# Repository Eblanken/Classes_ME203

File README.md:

# Classes_ME203
CAD and ECAD files for the ME203 manufacturing class.

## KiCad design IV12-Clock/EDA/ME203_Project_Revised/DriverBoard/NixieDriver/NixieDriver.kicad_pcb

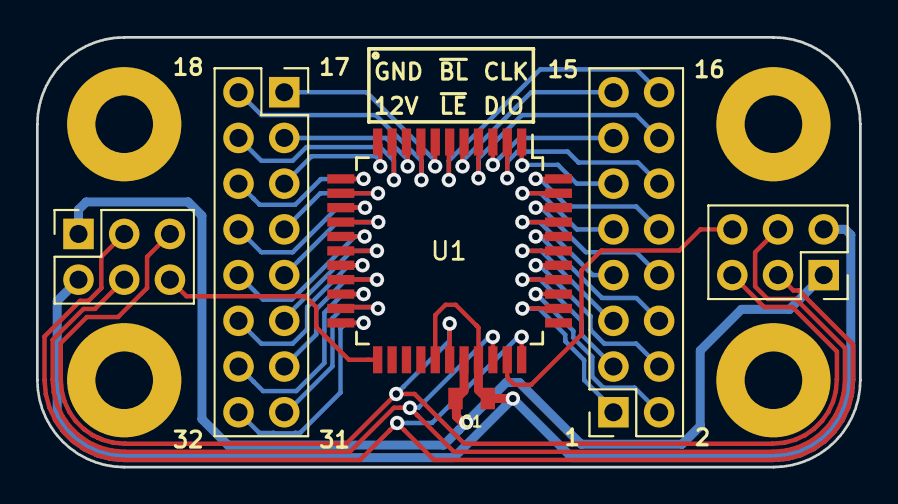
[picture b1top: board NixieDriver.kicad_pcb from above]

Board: 2 copper layers, 45.7 x 23.9 mm, 10 parts (0 on the bottom side), 39 nets.

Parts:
C1: 0.1UF-0805-100V; 0805
H1, H2, H3, H4: STANDOFF_ELECTRICAL; STANDOFF-ELECTRICAL
J1, J4: Conn_02x08_Counter_Clockwise; PinSocket_2x08_P2.54mm_Vertical
J2, J3: Conn_01x06; PinSocket_2x03_P2.54mm_Vertical
U1: HV5530PG-G-44PQF; PQFP-44_10x10mm_P0.8mm

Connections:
+12V: C1.1, J2.2, J3.2, U1.27, U1.30
/CLK: J2.5, J3.5, U1.28
/DI: J3.6, U1.32
/DO: J2.6, U1.23
/~BL: J2.3, J3.3, U1.33
/~LE: J2.4, J3.4, U1.31
GND: C1.2, J2.1, J3.1, U1.29
unnamed: J1.1, U1.7
unnamed: J1.2, U1.8
unnamed: J1.3, U1.9
unnamed: J1.4, U1.10
unnamed: J1.5, U1.11
unnamed: J1.6, U1.12
unnamed: J1.7, U1.13
unnamed: J1.8, U1.14
unnamed: J1.9, U1.15
unnamed: J1.10, U1.16
unnamed: J1.11, U1.17
unnamed: J1.12, U1.18
unnamed: J1.13, U1.19
unnamed: J1.14, U1.20
unnamed: J1.15, U1.21
unnamed: J1.16, U1.22
unnamed: J4.1, U1.35
unnamed: J4.2, U1.36
unnamed: J4.3, U1.37
unnamed: J4.4, U1.38
unnamed: J4.5, U1.39
unnamed: J4.6, U1.40
unnamed: J4.7, U1.41
unnamed: J4.8, U1.42
unnamed: J4.9, U1.43
unnamed: J4.10, U1.44
unnamed: J4.11, U1.1
unnamed: J4.12, U1.2
unnamed: J4.13, U1.3
unnamed: J4.14, U1.4
unnamed: J4.15, U1.5
unnamed: J4.16, U1.6

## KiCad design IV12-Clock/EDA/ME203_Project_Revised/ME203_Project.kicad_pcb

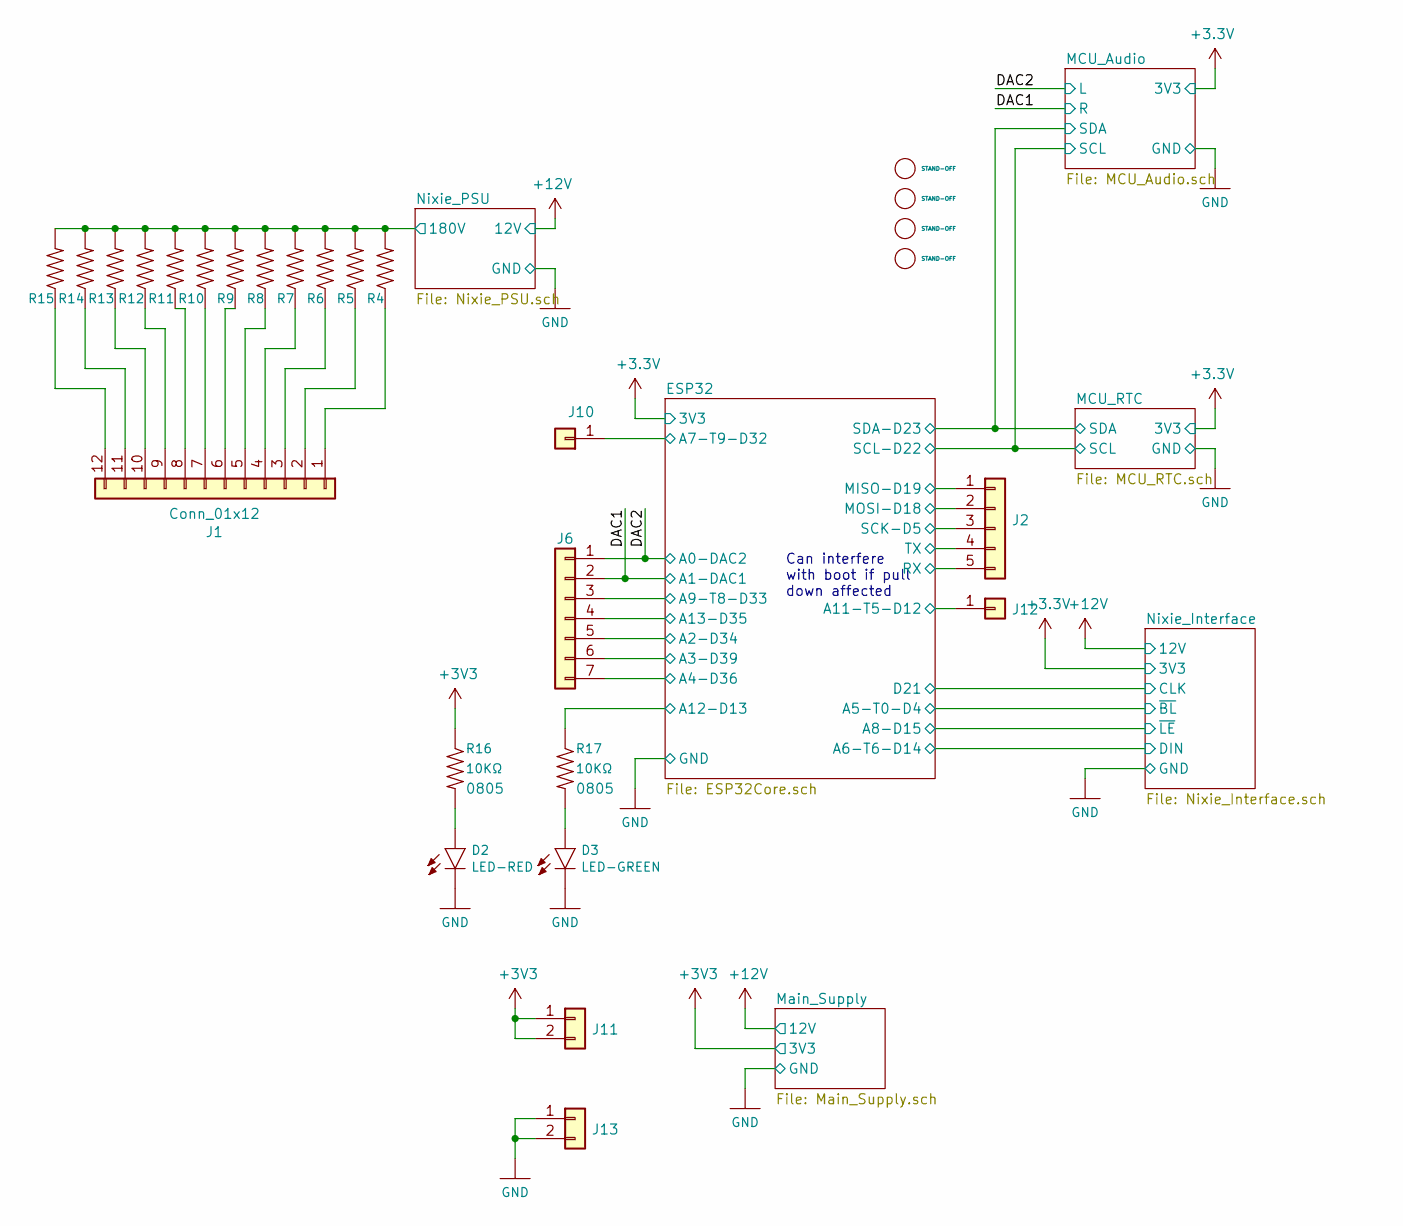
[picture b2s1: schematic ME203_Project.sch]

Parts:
D2: LED-RED; LED-0603
D3: LED-GREEN; LED-0603
H1, H2, H3, H4: STAND-OFF
J1: Conn_01x12; PinSocket_2x06_P2.54mm_Vertical
J2: Conn_01x05; PinHeader_1x05_P2.54mm_Vertical
J6: Conn_01x07; PinHeader_1x07_P2.54mm_Vertical
J10, J12: Conn_01x01; PinHeader_1x01_P2.54mm_Vertical
J11, J13: Conn_01x02; PinHeader_1x02_P2.54mm_Vertical
R4, R5, R6, R7, R8, R9, R10, R11, R12, R13, R14, R15: RESISTOR0805; 0805
R16, R17: 10KΩ; 0805

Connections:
+3V3: J11.1, J11.2, R16.1; also elsewhere on the board
/DAC1: J6.2; also elsewhere on the board
/DAC2: J6.1; also elsewhere on the board
/ESP32/A2-D34: J6.5; also elsewhere on the board
/ESP32/A3-D39: J6.6; also elsewhere on the board
/ESP32/A4-D36: J6.7; also elsewhere on the board
/ESP32/A7-T9-D32: J10.1; also elsewhere on the board
/ESP32/A9-T8-D33: J6.3; also elsewhere on the board
/ESP32/A11-T5-D12: J12.1; also elsewhere on the board
/ESP32/A12-D13: R17.1; also elsewhere on the board
/ESP32/A13-D35: J6.4; also elsewhere on the board
/ESP32/MISO-D19: J2.1; also elsewhere on the board
/ESP32/MOSI-D18: J2.2; also elsewhere on the board
/ESP32/RX: J2.5; also elsewhere on the board
/ESP32/SCK-D5: J2.3; also elsewhere on the board
/ESP32/TX: J2.4; also elsewhere on the board
/Nixie_PSU/180V: R4.2, R5.2, R6.2, R7.2, R8.2, R9.2, R10.2, R11.2, R12.2, R13.2, R14.2, R15.2; also elsewhere on the board
GND: D2.C, D3.C, J13.1, J13.2; also elsewhere on the board
unnamed: D2.A, R16.2
unnamed: D3.A, R17.2
unnamed: J1.1, R4.1
unnamed: J1.2, R5.1
unnamed: J1.3, R6.1
unnamed: J1.4, R7.1
unnamed: J1.5, R8.1
unnamed: J1.6, R9.1
unnamed: J1.7, R10.1
unnamed: J1.8, R11.1
unnamed: J1.9, R12.1
unnamed: J1.10, R13.1
unnamed: J1.11, R14.1
unnamed: J1.12, R15.1

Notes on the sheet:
Can interfere with boot if pull down affected

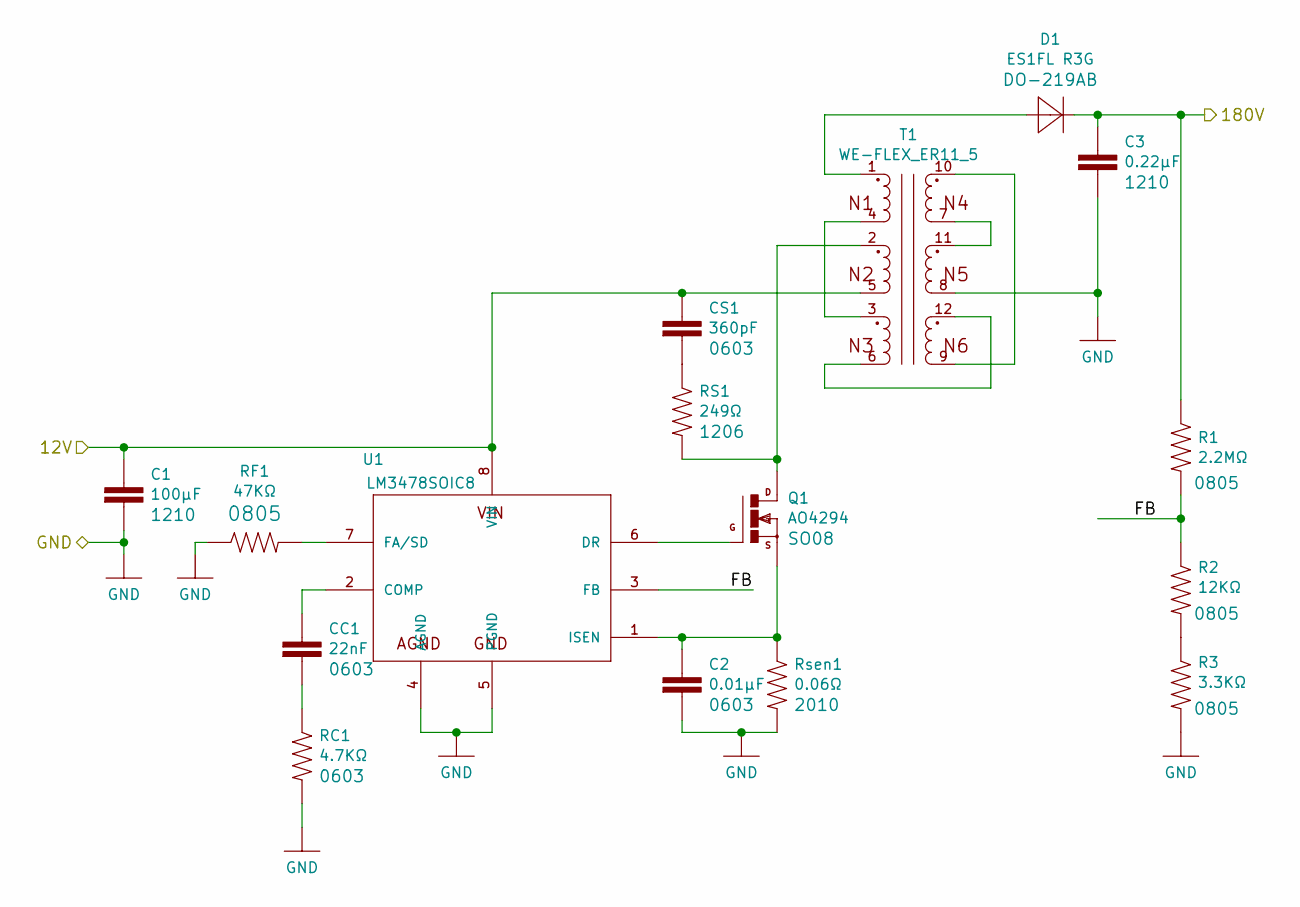
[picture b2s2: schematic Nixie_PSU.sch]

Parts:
C1: 100µF; C_1210_3225Metric; Digikey 311-2052-1-ND
C2: 0.01µF; C_0603_1608Metric; Digikey 311-3369-1-ND
C3: 0.22µF; C_1210_3225Metric; Digikey 445-2296-1-ND
CC1: 22nF; C_0603_1608Metric; Digikey 732-7935-1-ND
CS1: 360pF; C_0603_1608Metric; Digikey 490-1364-1-ND
D1: ES1FL R3G; nixiemisc-DO-219AB; Digikey ES1FL R3GCT-ND
Q1: AO4294; nixiemisc-SO-08; Digikey 785-1732-1-ND
R1: 2.2MΩ; 0603
R2: 12KΩ; 0805
R3: 3.3KΩ; 0805
RC1: 4.7KΩ; R_0603_1608Metric; Digikey RMCF0805FT4K70CT-ND
RF1: 47KΩ; R_0805_2012Metric; Digikey RMCF0805FT47K0CT-ND
RS1: 249Ω; R_1206_3216Metric; Digikey RNCP1206FTD249RCT-ND
Rsen1: 0.06Ω; R_2010_5025Metric; Digikey CSRN2010FK60L0CT-ND
T1: WE-FLEX_ER11_5; nixiemisc-WE-FLEX_ER11_5; Digikey 1297-1196-1-ND
U1: LM3478SOIC8; nixiemisc-SOIC8; Digikey 296-38111-1-ND

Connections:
+12V: C1.1, CS1.1, T1.5 (10), U1.8 (VIN); also elsewhere on the board
/Nixie_PSU/180V: C3.1, D1.C, R1.1; also elsewhere on the board
/Nixie_PSU/FB: R1.2, R2.1, U1.3 (FB)
GND: C1.2, C2.2, C3.2, R3.2, RC1.2, RF1.1, Rsen1.2, T1.8 (5), U1.4 (AGND), U1.5 (PGND); also elsewhere on the board
unnamed: C2.1, Q1.1 (S), Q1.2 (S), Q1.3 (S), Rsen1.1, U1.1 (ISEN)
unnamed: CC1.1, U1.2 (COMP)
unnamed: CC1.2, RC1.1
unnamed: CS1.2, RS1.1
unnamed: D1.A, T1.1
unnamed: Q1.4 (G), U1.6 (DR)
unnamed: Q1.5 (D), Q1.6 (D), Q1.7 (D), Q1.8 (D), RS1.2, T1.2 (11)
unnamed: R2.2, R3.1
unnamed: RF1.2, U1.7 (FA/SD)
unnamed: T1.3 (9), T1.4 (12)
unnamed: T1.9 (7), T1.10 (2)
unnamed: T1.7 (3), T1.11 (4)
unnamed: T1.6 (8), T1.12 (6)

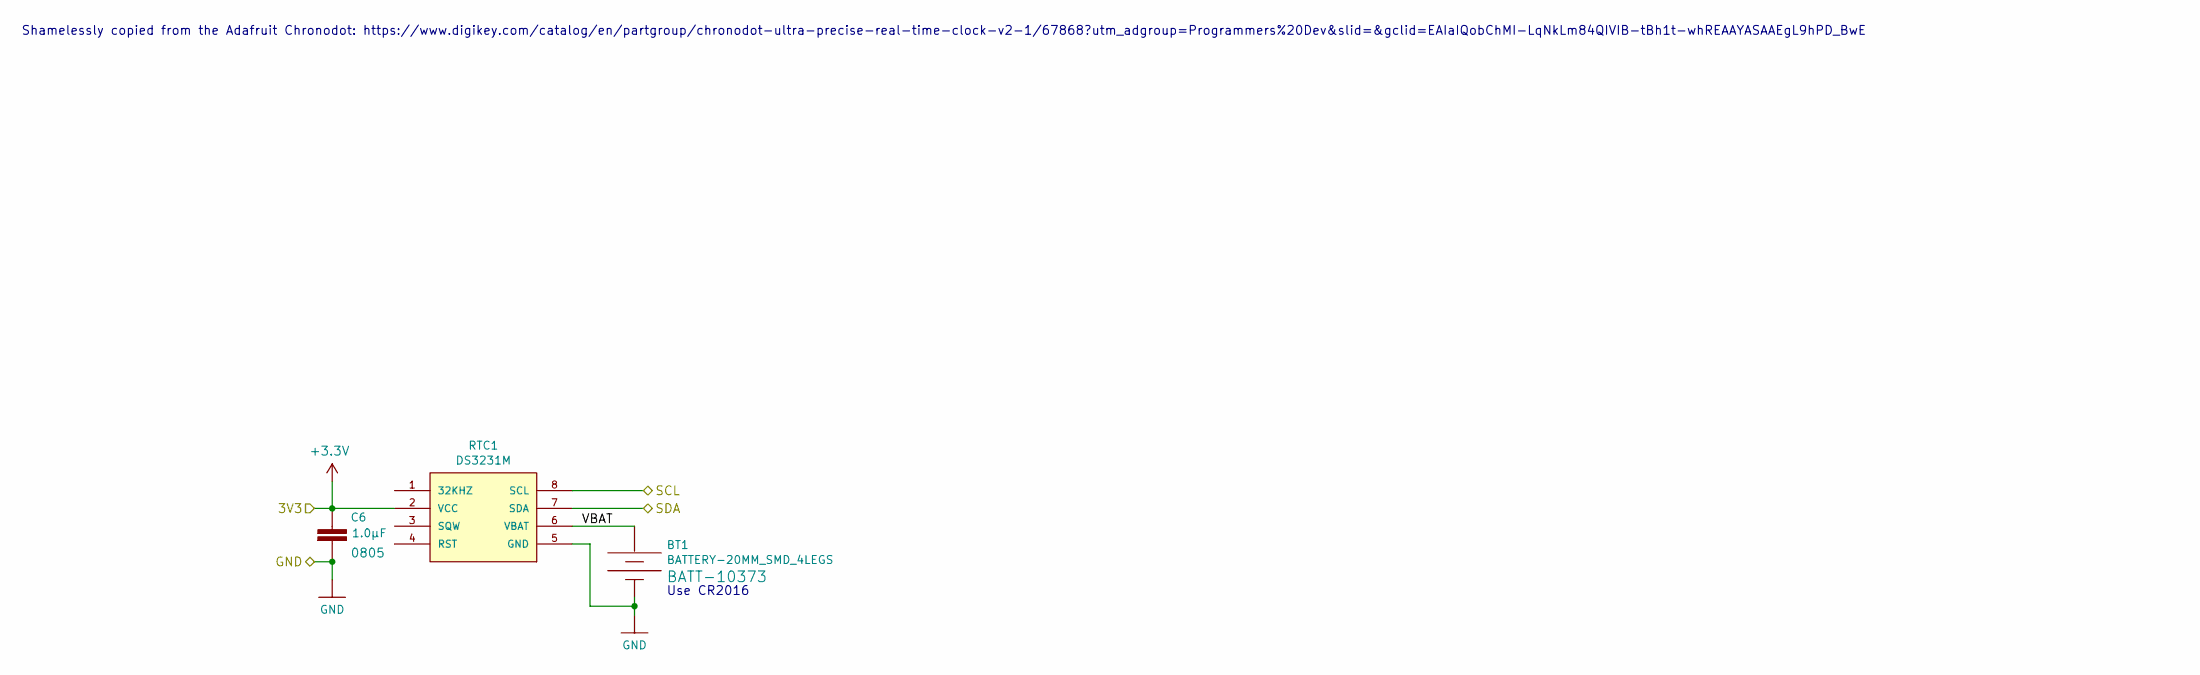
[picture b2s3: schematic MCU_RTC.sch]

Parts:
BT1: BATTERY-20MM_SMD_4LEGS; BATTCON_20MM_4LEGS
C6: 1.0µF; 0805
RTC1: DS3231M; SO08; Digikey DS3231MZ+-ND

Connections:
+: BT1.POSI (+), RTC1.6 (VBAT)
+3V3: C6.1, RTC1.2 (VCC); also elsewhere on the board
/MCU_Audio/SCL: RTC1.8 (SCL); also elsewhere on the board
/MCU_Audio/SDA: RTC1.7 (SDA); also elsewhere on the board
GND: BT1.NEGA (-), C6.2, RTC1.5 (GND); also elsewhere on the board

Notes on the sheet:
Shamelessly copied from the Adafruit Chronodot: https://www.digikey.com/catalog/en/partgroup/chronodot-ultra-precise-real-time-clock-v2-1/67868?utm_adgroup=Programmers%20Dev&slid=&gclid=EAIaIQobChMI-LqNkLm84QIVIB-tBh1t-whREAAYASAAEgL9hPD_BwE
Use CR2016

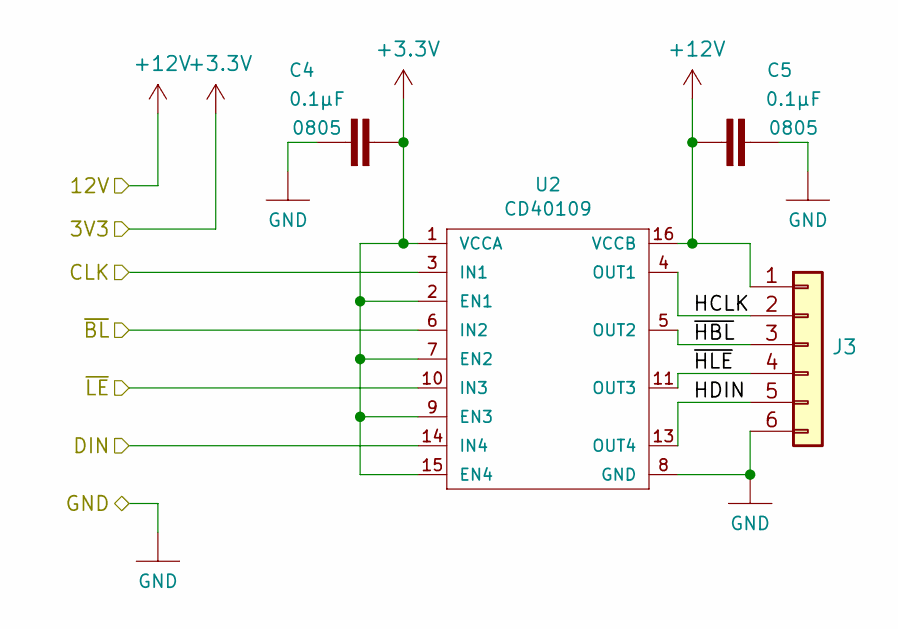
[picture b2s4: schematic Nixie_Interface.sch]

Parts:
C4, C5: 0.1µF; 0805
J3: Conn_01x06; PinSocket_1x06_P2.54mm_Vertical
U2: CD40109; nixiemisc-TSSOP-16; Digikey 296-12163-1-ND

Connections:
+3V3: C4.2, U2.1 (VCCA), U2.2 (EN1), U2.7 (EN2), U2.9 (EN3), U2.15 (EN4); also elsewhere on the board
+12V: C5.1, J3.1, U2.16 (VCCB); also elsewhere on the board
/ESP32/A5-T0-D4: U2.6 (IN2); also elsewhere on the board
/ESP32/A6-T6-D14: U2.14 (IN4); also elsewhere on the board
/ESP32/A8-D15: U2.10 (IN3); also elsewhere on the board
/Nixie_Interface/CLK: U2.3 (IN1); also elsewhere on the board
/Nixie_Interface/HCLK: J3.2, U2.4 (OUT1)
/Nixie_Interface/HDIN: J3.5, U2.13 (OUT4)
/Nixie_Interface/~HBL: J3.3, U2.5 (OUT2)
/Nixie_Interface/~HLE: J3.4, U2.11 (OUT3)
GND: C4.1, C5.2, J3.6, U2.8 (GND); also elsewhere on the board

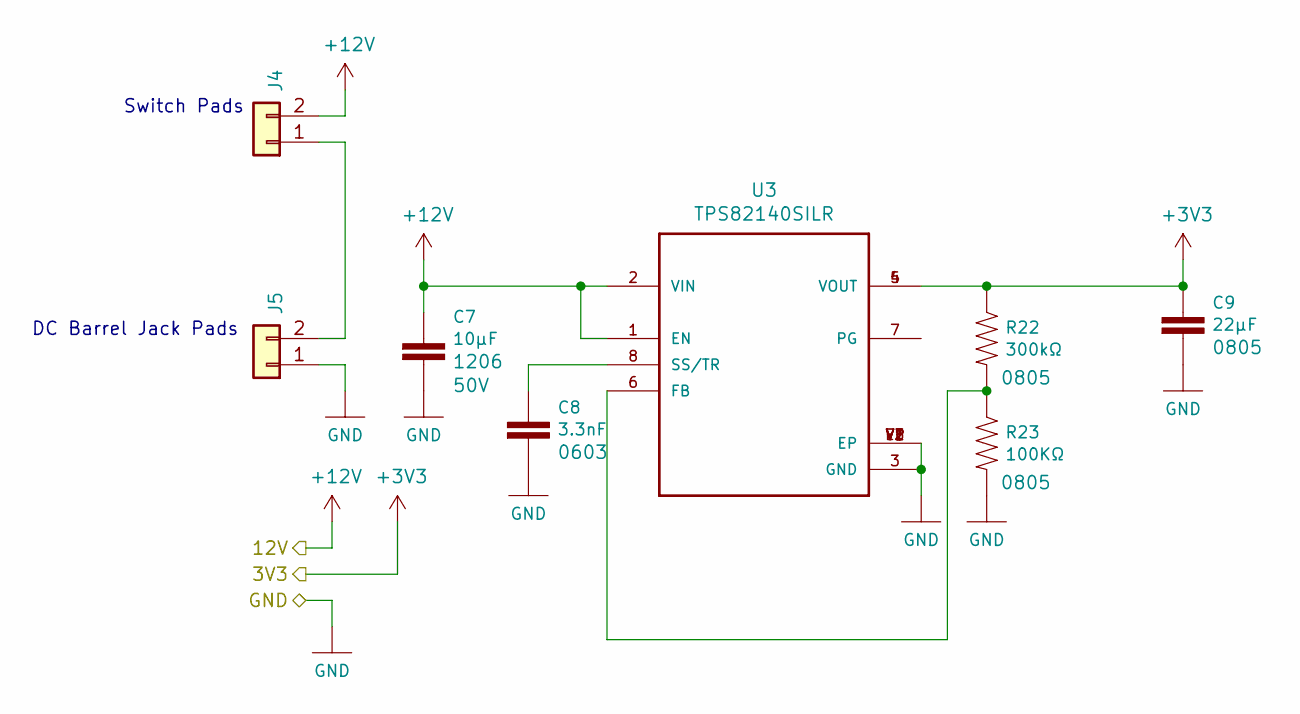
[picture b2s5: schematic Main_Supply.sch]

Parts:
C7: 10µF; 1206
C8: 3.3nF; 0603
C9: 22µF; 0805
J4, J5: Conn_01x02; PinSocket_1x02_P2.54mm_Vertical
R22: 300kΩ; 0805
R23: 100KΩ; 0805
U3: TPS82140SILR; PSON65P280X300X153-9N

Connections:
+3V3: C9.1, R22.1, U3.4 (VOUT), U3.5 (VOUT); also elsewhere on the board
+12V: C7.1, J4.2, U3.1 (EN), U3.2 (VIN); also elsewhere on the board
GND: C7.2, C8.2, C9.2, J5.1, R23.2, U3.3 (GND), U3.EP, U3.V1 (EP), U3.V2 (EP), U3.V3 (EP); also elsewhere on the board
unnamed: C8.1, U3.8 (SS/TR)
unnamed: J4.1, J5.2
unnamed: R22.2, R23.1, U3.6 (FB)

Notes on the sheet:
DC Barrel Jack Pads
Switch Pads

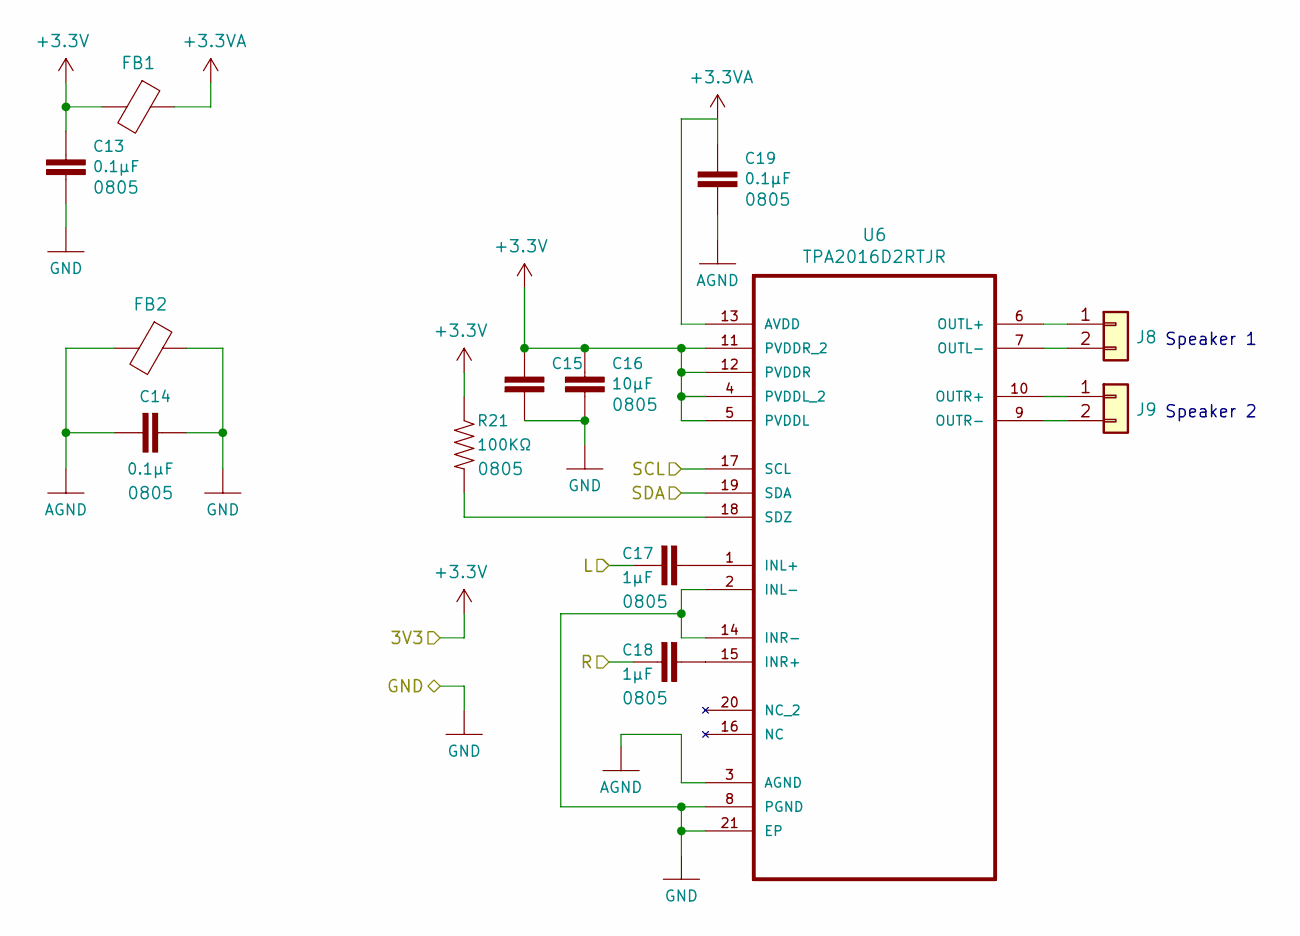
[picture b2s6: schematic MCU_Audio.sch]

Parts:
C13, C14, C19: 0.1µF; 0805
C15, C16: 10µF; 0805
C17, C18: 1µF; 0805
FB1, FB2: Ferrite_Bead; 0805
J8, J9: Conn_01x02; PinHeader_1x02_P2.54mm_Vertical
R21: 100KΩ; 0805
U6: TPA2016D2RTJR; QFN50P400X400X80-21N

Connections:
+3.3VA: C19.1, FB1.1, U6.13 (AVDD)
+3V3: C13.1, C15.1, C16.1, FB1.2, R21.1, U6.4 (PVDDL_2), U6.5 (PVDDL), U6.11 (PVDDR_2), U6.12 (PVDDR); also elsewhere on the board
/DAC1: C18.2; also elsewhere on the board
/DAC2: C17.2; also elsewhere on the board
/MCU_Audio/SCL: U6.17 (SCL); also elsewhere on the board
/MCU_Audio/SDA: U6.19 (SDA); also elsewhere on the board
AGND: C14.2, C19.2, FB2.2, U6.3 (AGND)
GND: C13.2, C14.1, C15.2, C16.2, FB2.1, U6.2 (INL-), U6.8 (PGND), U6.14 (INR-), U6.21 (EP); also elsewhere on the board
unnamed: C17.1, U6.1 (INL+)
unnamed: C18.1, U6.15 (INR+)
unnamed: J8.1, U6.6 (OUTL+)
unnamed: J8.2, U6.7 (OUTL-)
unnamed: J9.1, U6.10 (OUTR+)
unnamed: J9.2, U6.9 (OUTR-)
unnamed: R21.2, U6.18 (SDZ)

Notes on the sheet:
Speaker 1
Speaker 2

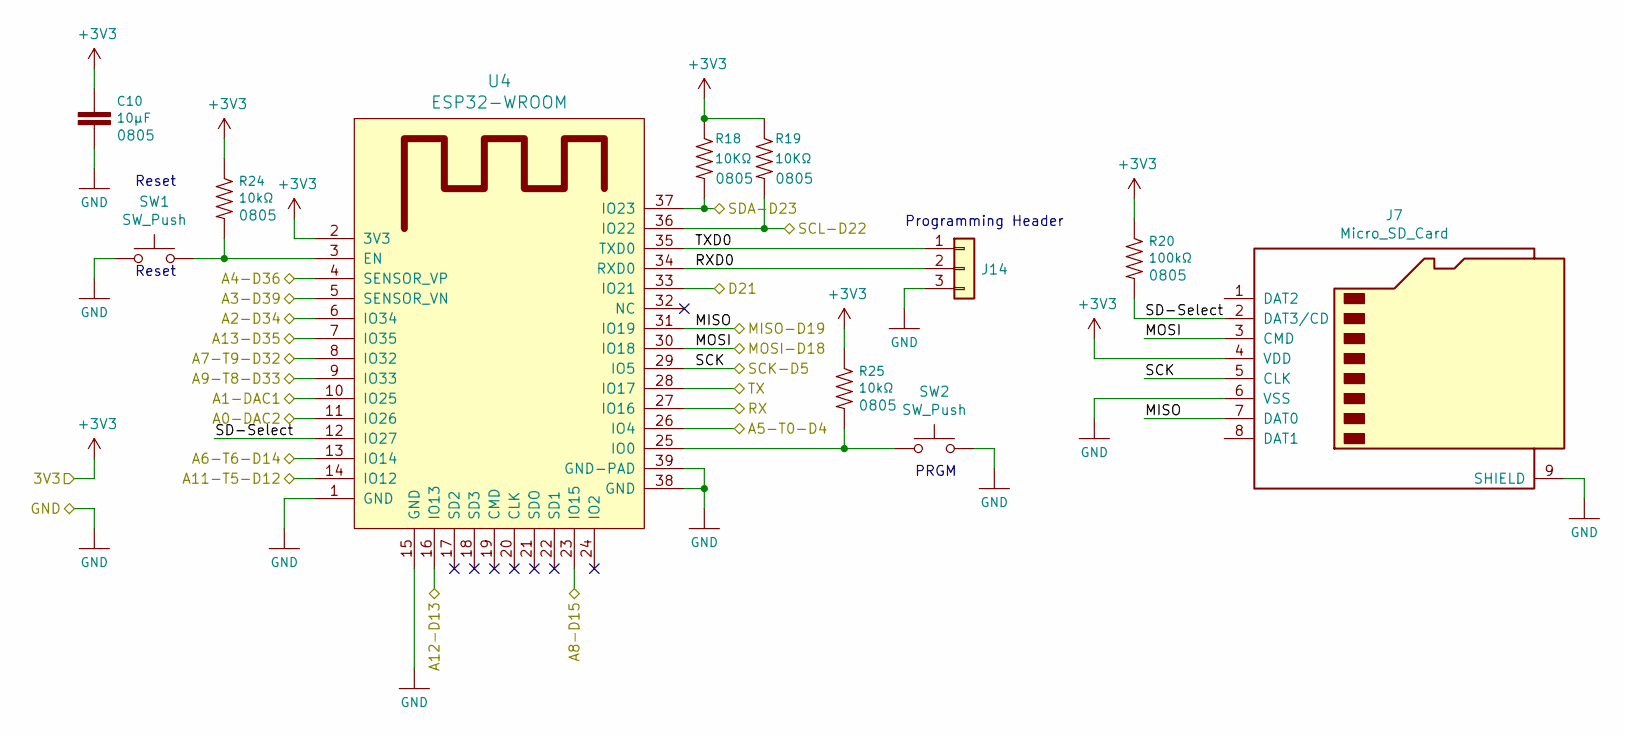
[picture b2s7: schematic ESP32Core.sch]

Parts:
C10: 10µF; 0805
J7: Micro_SD_Card; microSD_HC_Wuerth_693072010801
J14: Conn_01x03; PinHeader_1x03_P2.54mm_Vertical
R18, R19: 10KΩ; 0805
R20: 100kΩ; 0805
R24, R25: 10kΩ; 0805
SW1: SW_Push; TACTILE_SWITCH_SMD_5.2MM_Corrected; Digikey CKN9104CT-ND
SW2: SW_Push; TACTILE_SWITCH_SMD_5.2MM_Corrected
U4: ESP32-WROOM

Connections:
+3V3: C10.1, J7.4 (VDD), R18.1, R19.1, R20.1, R24.1, R25.1, U4.2 (3V3); also elsewhere on the board
/DAC1: U4.10 (IO25); also elsewhere on the board
/DAC2: U4.11 (IO26); also elsewhere on the board
/ESP32/A2-D34: U4.6 (IO34); also elsewhere on the board
/ESP32/A3-D39: U4.5 (SENSOR_VN); also elsewhere on the board
/ESP32/A4-D36: U4.4 (SENSOR_VP); also elsewhere on the board
/ESP32/A5-T0-D4: U4.26 (IO4); also elsewhere on the board
/ESP32/A6-T6-D14: U4.13 (IO14); also elsewhere on the board
/ESP32/A7-T9-D32: U4.8 (IO32); also elsewhere on the board
/ESP32/A8-D15: U4.23 (IO15); also elsewhere on the board
/ESP32/A9-T8-D33: U4.9 (IO33); also elsewhere on the board
/ESP32/A11-T5-D12: U4.14 (IO12); also elsewhere on the board
/ESP32/A12-D13: U4.16 (IO13); also elsewhere on the board
/ESP32/A13-D35: U4.7 (IO35); also elsewhere on the board
/ESP32/MISO-D19: J7.7 (DAT0), U4.31 (IO19); also elsewhere on the board
/ESP32/MOSI-D18: J7.3 (CMD), U4.30 (IO18); also elsewhere on the board
/ESP32/RX: U4.27 (IO16); also elsewhere on the board
/ESP32/RXD0: J14.2, U4.34 (RXD0)
/ESP32/SCK-D5: J7.5 (CLK), U4.29 (IO5); also elsewhere on the board
/ESP32/SD-Select: J7.2 (DAT3/CD), R20.2, U4.12 (IO27)
/ESP32/TX: U4.28 (IO17); also elsewhere on the board
/ESP32/TXD0: J14.1, U4.35 (TXD0)
/MCU_Audio/SCL: R19.2, U4.36 (IO22); also elsewhere on the board
/MCU_Audio/SDA: R18.2, U4.37 (IO23); also elsewhere on the board
/Nixie_Interface/CLK: U4.33 (IO21); also elsewhere on the board
GND: C10.2, J7.6 (VSS), J7.9 (SHIELD), J14.3, SW1.1, SW2.2, U4.1 (GND), U4.15 (GND), U4.38 (GND), U4.39 (GND-PAD); also elsewhere on the board
unnamed: R24.2, SW1.2, U4.3 (EN)
unnamed: R25.2, SW2.1, U4.25 (IO0)

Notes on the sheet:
Reset
PRGM
Programming Header

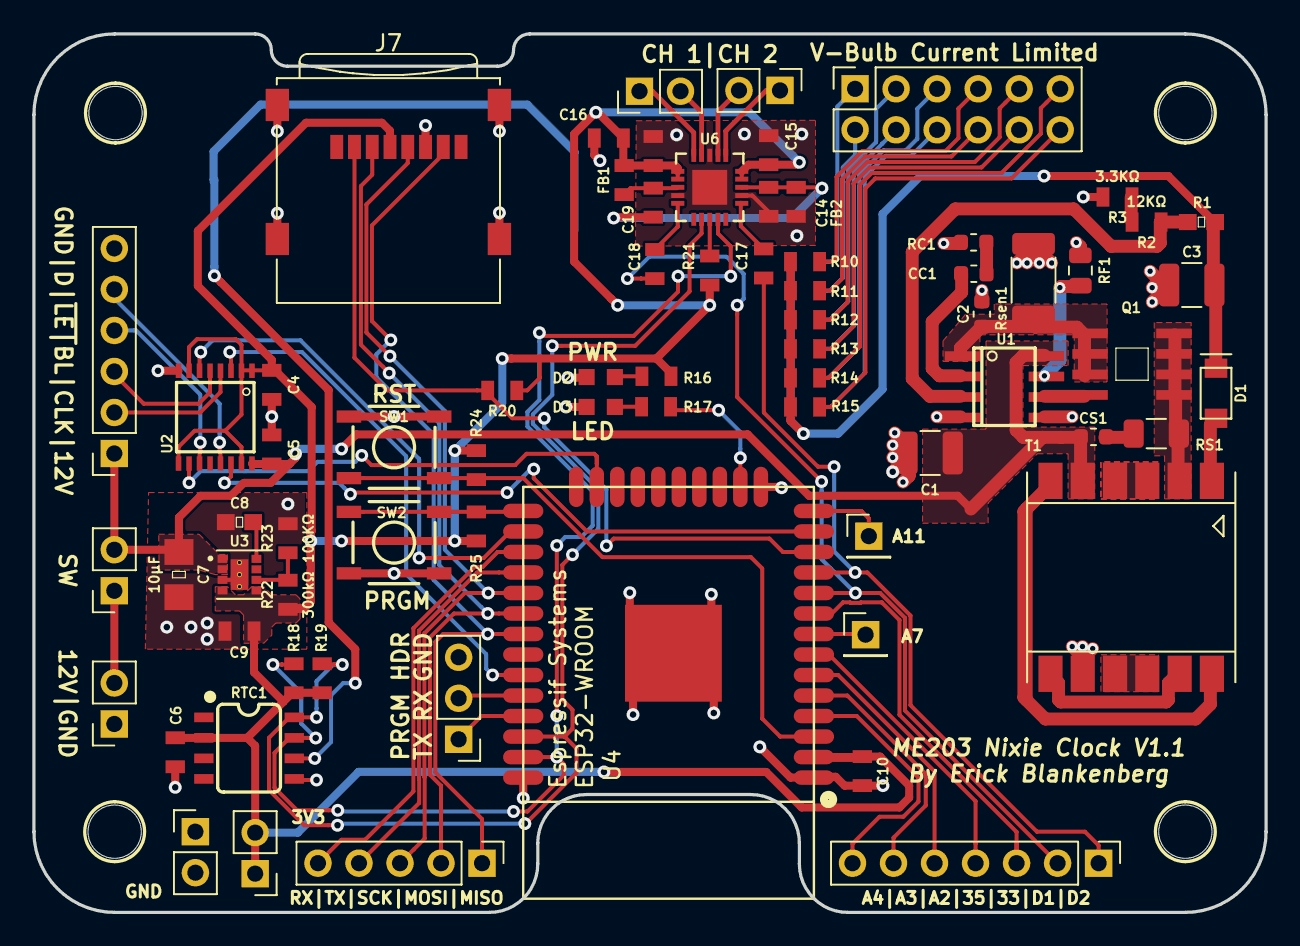
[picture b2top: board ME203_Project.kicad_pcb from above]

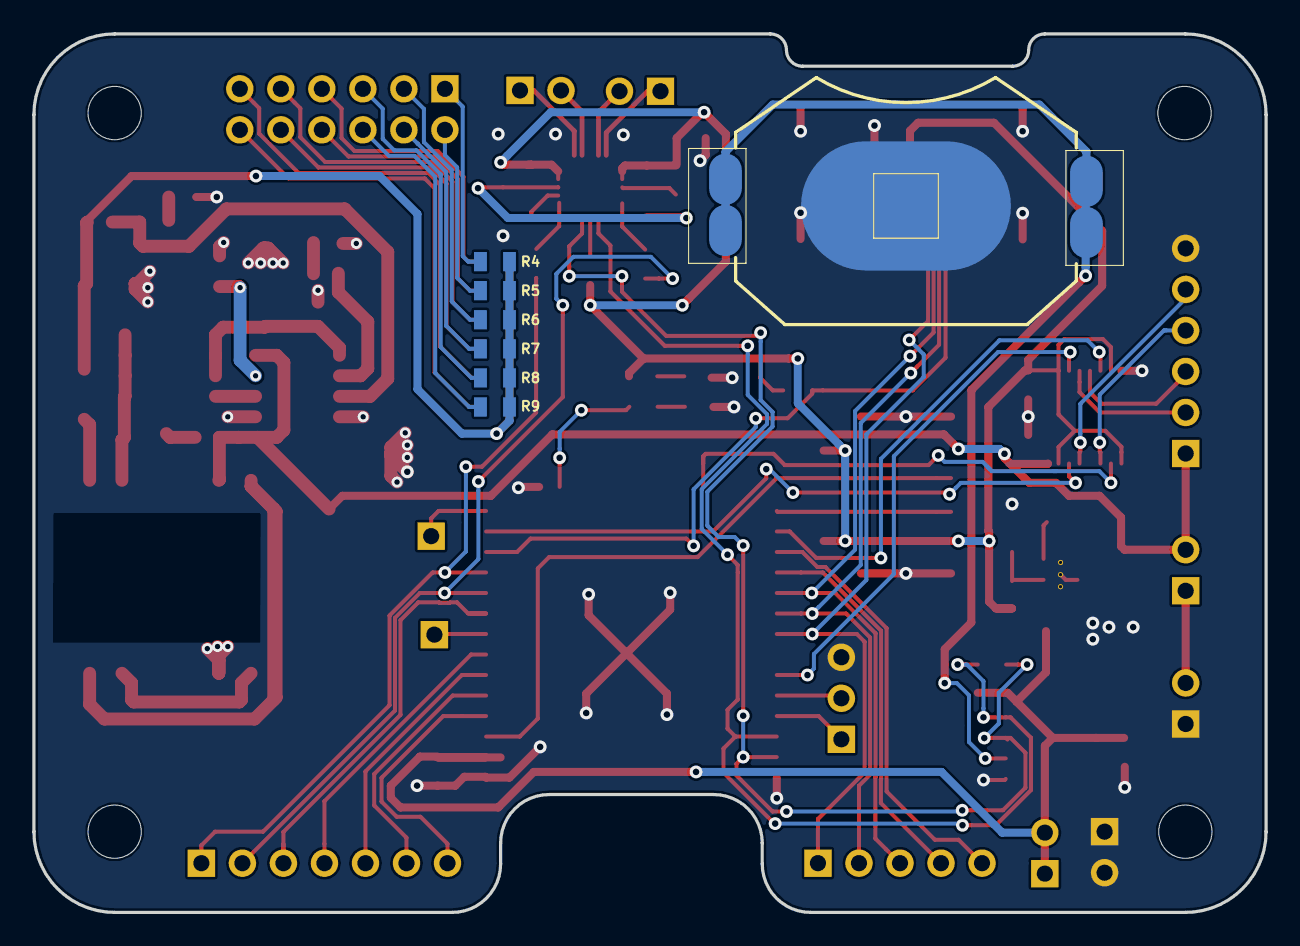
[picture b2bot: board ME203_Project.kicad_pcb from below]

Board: 2 copper layers, 76.3 x 54.4 mm, 82 parts (7 on the bottom side), 75 nets.

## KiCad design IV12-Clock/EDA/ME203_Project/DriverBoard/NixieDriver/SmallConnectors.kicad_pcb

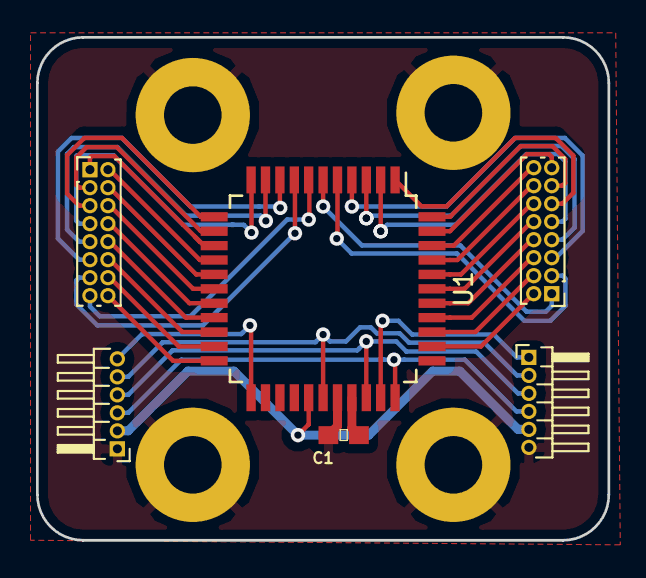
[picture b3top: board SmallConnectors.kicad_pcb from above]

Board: 2 copper layers, 31.8 x 27.9 mm, 10 parts (0 on the bottom side), 39 nets.

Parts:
C1: 0.1UF-0603-100V-10%; 0603
H1, H2, H3, H4: STANDOFF_ELECTRICAL; STANDOFF-ELECTRICAL
J1, J4: Conn_02x08_Odd_Even; PinHeader_2x08_P1.00mm_Vertical
J2, J3: Conn_01x06; PinHeader_1x06_P1.00mm_Horizontal
U1: HV5530PG-G-44PQF; PQFP-44_10x10mm_P0.8mm

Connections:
+12V: C1.1, J2.2, J3.5, U1.27, U1.30
/CLK: J2.5, J3.2, U1.28
/DI: J3.1, U1.32
/DO: J2.6, U1.23
/~BL: J2.3, J3.4, U1.33
/~LE: J2.4, J3.3, U1.31
GND: C1.2, H1.P1, H2.P1, H3.P1, H4.P1, J2.1, J3.6, U1.29
unnamed: J1.1, U1.14
unnamed: J1.2, U1.15
unnamed: J1.3, U1.13
unnamed: J1.4, U1.16
unnamed: J1.5, U1.12
unnamed: J1.6, U1.17
unnamed: J1.7, U1.11
unnamed: J1.8, U1.18
unnamed: J1.9, U1.10
unnamed: J1.10, U1.19
unnamed: J1.11, U1.9
unnamed: J1.12, U1.20
unnamed: J1.13, U1.8
unnamed: J1.14, U1.21
unnamed: J1.15, U1.7
unnamed: J1.16, U1.22
unnamed: J4.1, U1.6
unnamed: J4.2, U1.35
unnamed: J4.3, U1.5
unnamed: J4.4, U1.36
unnamed: J4.5, U1.4
unnamed: J4.6, U1.37
unnamed: J4.7, U1.3
unnamed: J4.8, U1.38
unnamed: J4.9, U1.2
unnamed: J4.10, U1.39
unnamed: J4.11, U1.1
unnamed: J4.12, U1.40
unnamed: J4.13, U1.44
unnamed: J4.14, U1.41
unnamed: J4.15, U1.43
unnamed: J4.16, U1.42

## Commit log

2018-12-15 [initial] Added files for modular clock
2019-04-27 finished driver PCBs, main board WIP
2019-06-07 Code KWS, working on actual time.
2019-06-07 RTC does not talk, figured out buttons
2019-06-10 Changed IV12 display function format, fixed display method and got rid of flicker as a result, buttons work with press and release
2019-06-11 Added touch buttons for speakers (untested)
